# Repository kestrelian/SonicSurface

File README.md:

# SonicSurface
An Open ultrasonic phased-array for applications in acoustic levitation, haptic feedback, directive audio and many more.

## What's new here?
For our Capstone project, we designed a downsized array PCB for an 8 x 8 system. One FGPA (Waveshare/Altera) is responsible for 2 PCBs in contrast to the original SonicSurface implementation of 1 FGPA/baord.

# Contents of this Repository
Algorithms - Algorithms to generate different patterns (unchanged)
Electronics - PCB gerber files and bill of materials (PCB changed)
Firmware - Code to be upload in the FPGA boards that control the arrays (unchanged)
Mech - Mechanical parts for 3d printing or lasercutting (unchanged)

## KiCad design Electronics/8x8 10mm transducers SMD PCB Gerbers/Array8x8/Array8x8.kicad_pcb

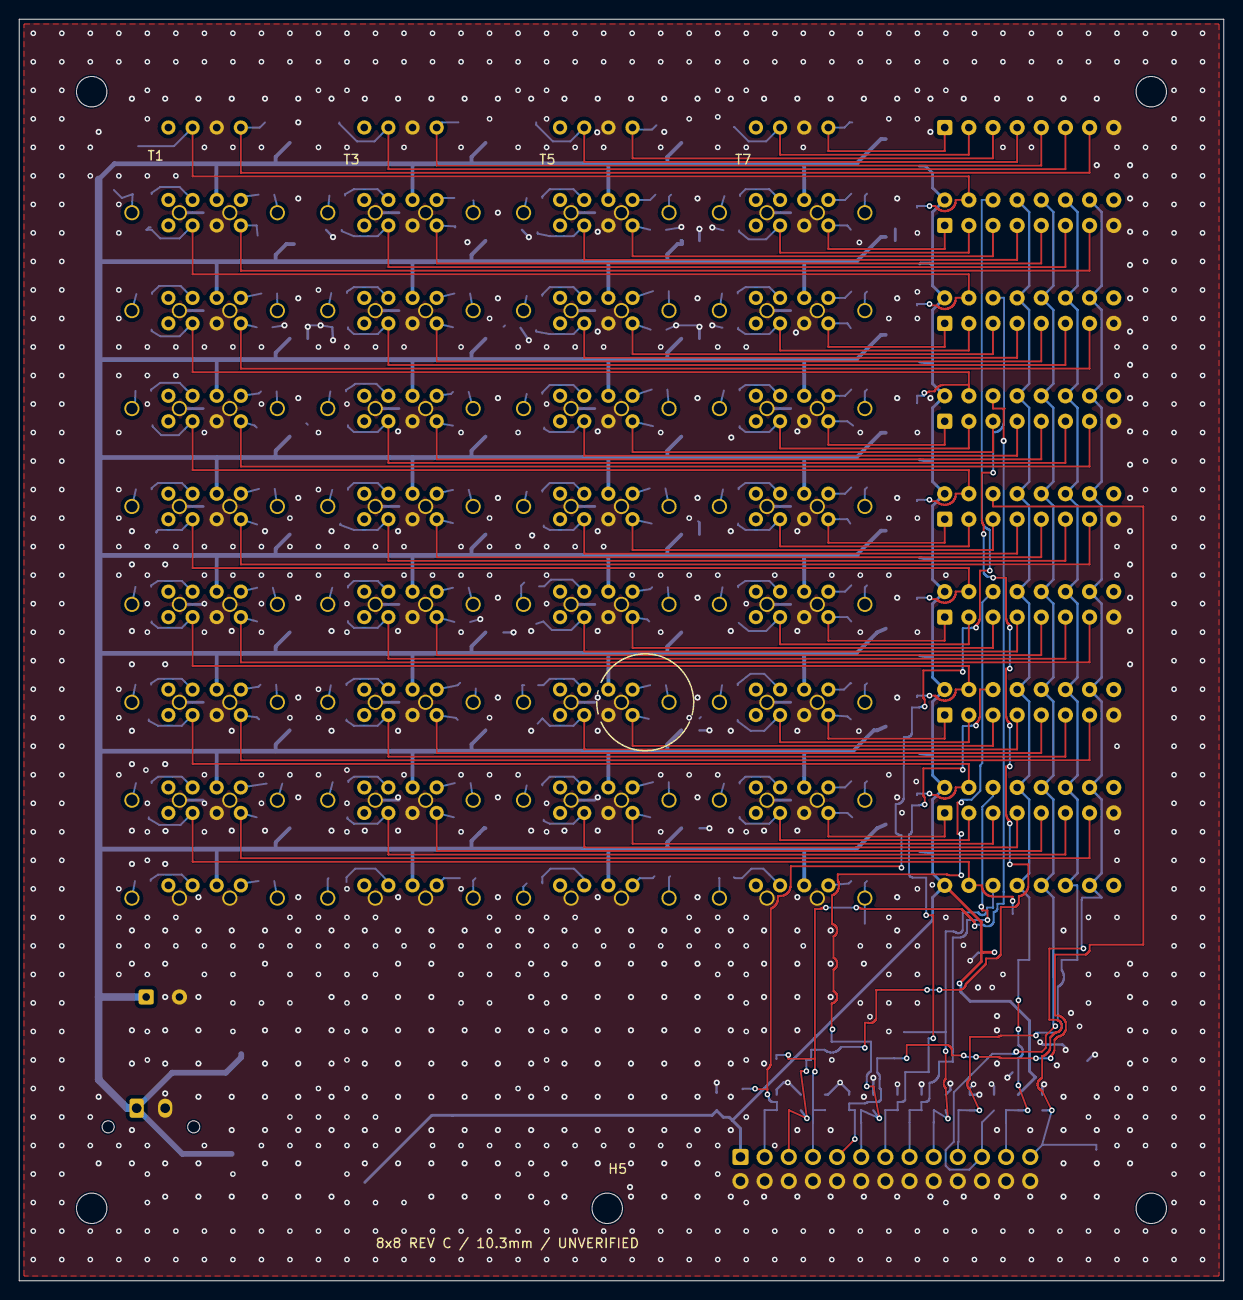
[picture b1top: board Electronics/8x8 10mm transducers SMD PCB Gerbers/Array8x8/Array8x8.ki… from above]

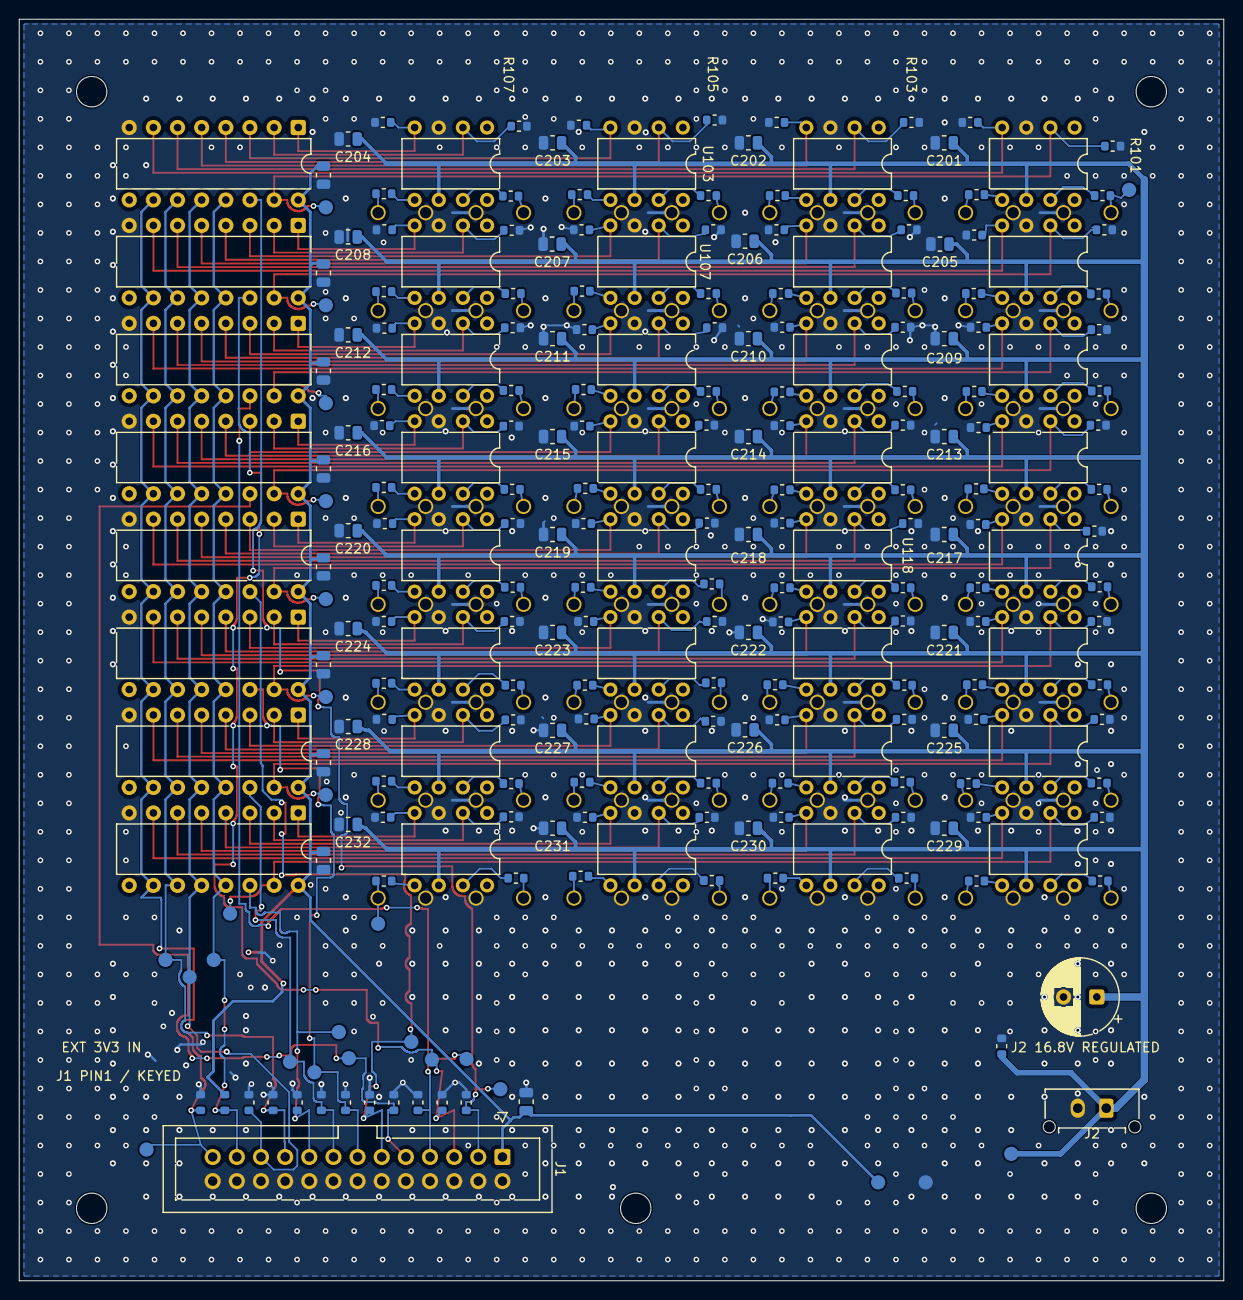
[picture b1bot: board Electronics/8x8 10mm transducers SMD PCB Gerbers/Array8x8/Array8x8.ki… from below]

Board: 2 copper layers, 126.7 x 132.7 mm, 319 parts (250 on the bottom side), 207 nets.

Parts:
C1: 220uF 35V low ESR; CP_Radial_D8.0mm_P3.50mm
C2, C10, C11, C12, C13, C14, C15, C16, C17, C201, C202, C203, C204, C205, C206, C207, C208, C209, C210, C211, C212, C213, C214, C215, C216, C217, C218, C219, C220, C221, C222, C223, C224, C225, C226, C227, C228, C229, C230, C231, C232: 1uF 50V X7R; C_0805_2012Metric
H1, H2, H3, H4, H5: MountingHole_3.2mm_M3
J1: KEYED IDC26 / 100mm MAX; IDC-Header_2x13_P2.54mm_Vertical
J2: REGULATED DRIVER POWER ONLY; FP_910b6471cdf1
R1, R20, R21, R22, R23, R24, R25, R26, R27, R28, R29, R30, R31, R101, R102, R103, R104, R105, R106, R107, R108, R109, R110, R111, R112, R113, R114, R115, R116, R117, R118, R119, R120, R121, R122, R123, R124, R125, R126, R127, R128, R129, R130, R131, R132, R133, R134, R135, R136, R137, R138, R139, R140, R141, R142, R143, R144, R145, R146, R147, R148, R149, R150, R151, R152, R153, R154, R155, R156, R157, R158, R159, R160, R161, R162, R163, R164: 10k; R_0603_1608Metric
R201, R202, R203, R204, R205, R206, R207, R208, R209, R210, R211, R212, R213, R214, R215, R216, R217, R218, R219, R220, R221, R222, R223, R224, R225, R226, R227, R228, R229, R230, R231, R232, R233, R234, R235, R236, R237, R238, R239, R240, R241, R242, R243, R244, R245, R246, R247, R248, R249, R250, R251, R252, R253, R254, R255, R256, R257, R258, R259, R260, R261, R262, R263, R264: 22R; R_0603_1608Metric
T1, T2, T3, T4, T5, T6, T7, T8, T9, T10, T11, T12, T13, T14, T15, T16, T17, T18, T19, T20, T21, T22, T23, T24, T25, T26, T27, T28, T29, T30, T31, T32, T33, T34, T35, T36, T37, T38, T39, T40, T41, T42, T43, T44, T45, T46, T47, T48, T49, T50, T51, T52, T53, T54, T55, T56, T57, T58, T59, T60, T61, T62, T63, T64: MA40S4S; MA40S4S_P5mm
TP1: GND; TestPoint_Pad_D1.5mm
TP2: +3V3; TestPoint_Pad_D1.5mm
TP3: VDRV; TestPoint_Pad_D1.5mm
TP4: SCLK; TestPoint_Pad_D1.5mm
TP5: LATCH; TestPoint_Pad_D1.5mm
TP6: OE_LOCAL_N; TestPoint_Pad_D1.5mm
TP8: DRV00; TestPoint_Pad_D1.5mm
TP9: DRV63; TestPoint_Pad_D1.5mm
TP10: Q00; TestPoint_Pad_D1.5mm
TP11: Q08; TestPoint_Pad_D1.5mm
TP12: Q16; TestPoint_Pad_D1.5mm
TP13: Q24; TestPoint_Pad_D1.5mm
TP14: Q32; TestPoint_Pad_D1.5mm
TP15: Q40; TestPoint_Pad_D1.5mm
TP16: Q48; TestPoint_Pad_D1.5mm
TP17: Q56; TestPoint_Pad_D1.5mm
TP18: DATA0_RX; TestPoint_Pad_D1.5mm
TP19: DATA1_RX; TestPoint_Pad_D1.5mm
TP20: DATA2_RX; TestPoint_Pad_D1.5mm
TP21: DATA3_RX; TestPoint_Pad_D1.5mm
TP22: DATA4_RX; TestPoint_Pad_D1.5mm
TP23: DATA5_RX; TestPoint_Pad_D1.5mm
TP24: DATA6_RX; TestPoint_Pad_D1.5mm
TP25: DATA7_RX; TestPoint_Pad_D1.5mm
TP26: CLR_N_RX; TestPoint_Pad_D1.5mm
U1, U2, U3, U4, U5, U6, U7, U8: SN74HC595N DIP-16; DIP-16_W7.62mm
U101, U102, U103, U104, U105, U106, U107, U108, U109, U110, U111, U112, U113, U114, U115, U116, U117, U118, U119, U120, U121, U122, U123, U124, U125, U126, U127, U128, U129, U130, U131, U132: TC4427EPA DIP-8; DIP-8_W7.62mm

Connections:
+3V3: C2.1, C10.1, C11.1, C12.1, C13.1, C14.1, C15.1, C16.1, C17.1, J1.1, R31.2, TP2.1, U1.16, U2.16, U3.16, U4.16, U5.16, U6.16, U7.16, U8.16
CLR_N_RX: J1.25, R30.1, TP26.1, U1.10, U2.10, U3.10, U4.10, U5.10, U6.10, U7.10, U8.10
DATA0_RX: J1.3, R20.1, TP18.1, U1.14
DATA1_RX: J1.5, R21.1, TP19.1, U2.14
DATA2_RX: J1.7, R22.1, TP20.1, U3.14
DATA3_RX: J1.9, R23.1, TP21.1, U4.14
DATA4_RX: J1.11, R24.1, TP22.1, U5.14
DATA5_RX: J1.13, R25.1, TP23.1, U6.14
DATA6_RX: J1.15, R26.1, TP24.1, U7.14
DATA7_RX: J1.17, R27.1, TP25.1, U8.14
DRV00: R201.2, T1.1, TP8.1
DRV01: R202.2, T2.1
DRV02: R203.2, T3.1
DRV03: R204.2, T4.1
DRV04: R205.2, T5.1
DRV05: R206.2, T6.1
DRV06: R207.2, T7.1
DRV07: R208.2, T8.1
DRV08: R209.2, T9.1
DRV09: R210.2, T10.1
DRV10: R211.2, T11.1
DRV11: R212.2, T12.1
DRV12: R213.2, T13.1
DRV13: R214.2, T14.1
DRV14: R215.2, T15.1
DRV15: R216.2, T16.1
DRV16: R217.2, T17.1
DRV17: R218.2, T18.1
DRV18: R219.2, T19.1
DRV19: R220.2, T20.1
DRV20: R221.2, T21.1
DRV21: R222.2, T22.1
DRV22: R223.2, T23.1
DRV23: R224.2, T24.1
DRV24: R225.2, T25.1
DRV25: R226.2, T26.1
DRV26: R227.2, T27.1
DRV27: R228.2, T28.1
DRV28: R229.2, T29.1
DRV29: R230.2, T30.1
DRV30: R231.2, T31.1
DRV31: R232.2, T32.1
DRV32: R233.2, T33.1
DRV33: R234.2, T34.1
DRV34: R235.2, T35.1
DRV35: R236.2, T36.1
DRV36: R237.2, T37.1
DRV37: R238.2, T38.1
DRV38: R239.2, T39.1
DRV39: R240.2, T40.1
DRV40: R241.2, T41.1
DRV41: R242.2, T42.1
DRV42: R243.2, T43.1
DRV43: R244.2, T44.1
DRV44: R245.2, T45.1
DRV45: R246.2, T46.1
DRV46: R247.2, T47.1
DRV47: R248.2, T48.1
DRV48: R249.2, T49.1
DRV49: R250.2, T50.1
DRV50: R251.2, T51.1
DRV51: R252.2, T52.1
DRV52: R253.2, T53.1
DRV53: R254.2, T54.1
DRV54: R255.2, T55.1
DRV55: R256.2, T56.1
DRV56: R257.2, T57.1
DRV57: R258.2, T58.1
DRV58: R259.2, T59.1
DRV59: R260.2, T60.1
DRV60: R261.2, T61.1
DRV61: R262.2, T62.1
DRV62: R263.2, T63.1
DRV63: R264.2, T64.1, TP9.1
GND: C1.2, C2.2, C10.2, C11.2, C12.2, C13.2, C14.2, C15.2, C16.2, C17.2, C201.2, C202.2, C203.2, C204.2, C205.2, C206.2, C207.2, C208.2, C209.2, C210.2, C211.2, C212.2, C213.2, C214.2, C215.2, C216.2, C217.2, C218.2, C219.2, C220.2, C221.2, C222.2, C223.2, C224.2, C225.2, C226.2, C227.2, C228.2, C229.2, C230.2, C231.2, C232.2, J1.2, J1.4, J1.6, J1.8, J1.10, J1.12, J1.14, J1.16, J1.18, J1.20, J1.22, J1.24, J1.26, J2.2, R1.2, R20.2, R21.2, R22.2, R23.2, R24.2, R25.2, R26.2, R27.2, R28.2, R29.2, R30.2, R101.2, R102.2, R103.2, R104.2, R105.2, R106.2, R107.2, R108.2, R109.2, R110.2, R111.2, R112.2, R113.2, R114.2, R115.2, R116.2, R117.2, R118.2, R119.2, R120.2, R121.2, R122.2, R123.2, R124.2, R125.2, R126.2, R127.2, R128.2, R129.2, R130.2, R131.2, R132.2, R133.2, R134.2, R135.2, R136.2, R137.2, R138.2, R139.2, R140.2, R141.2, R142.2, R143.2, R144.2, R145.2, R146.2, R147.2, R148.2, R149.2, R150.2, R151.2, R152.2, R153.2, R154.2, R155.2, R156.2, R157.2, R158.2, R159.2, R160.2, R161.2, R162.2, R163.2, R164.2, T1.2, T2.2, T3.2, T4.2, T5.2, T6.2, T7.2, T8.2, T9.2, T10.2, T11.2, T12.2, T13.2, T14.2, T15.2, T16.2, T17.2, T18.2, T19.2, T20.2, T21.2, T22.2, T23.2, T24.2, T25.2, T26.2, T27.2, T28.2, T29.2, T30.2, T31.2, T32.2, T33.2, T34.2, T35.2, T36.2, T37.2, T38.2, T39.2, T40.2, T41.2, T42.2, T43.2, T44.2, T45.2, T46.2, T47.2, T48.2, T49.2, T50.2, T51.2, T52.2, T53.2, T54.2, T55.2, T56.2, T57.2, T58.2, T59.2, T60.2, T61.2, T62.2, T63.2, T64.2, TP1.1, U1.8, U2.8, U3.8, U4.8, U5.8, U6.8, U7.8, U8.8, U101.3, U102.3, U103.3, U104.3, U105.3, U106.3, U107.3, U108.3, U109.3, U110.3, U111.3, U112.3, U113.3, U114.3, U115.3, U116.3, U117.3, U118.3, U119.3, U120.3, U121.3, U122.3, U123.3, U124.3, U125.3, U126.3, U127.3, U128.3, U129.3, U130.3, U131.3, U132.3
LATCH_RX: J1.21, R29.1, TP5.1, U1.12, U2.12, U3.12, U4.12, U5.12, U6.12, U7.12, U8.12
OE_N_RX: J1.23, R31.1, TP6.1, U1.13, U2.13, U3.13, U4.13, U5.13, U6.13, U7.13, U8.13
OUT00: R201.1, U101.7
OUT01: R202.1, U101.5
OUT02: R203.1, U102.7
OUT03: R204.1, U102.5
OUT04: R205.1, U103.7
OUT05: R206.1, U103.5
OUT06: R207.1, U104.7
OUT07: R208.1, U104.5
OUT08: R209.1, U105.7
OUT09: R210.1, U105.5
OUT10: R211.1, U106.7
OUT11: R212.1, U106.5
OUT12: R213.1, U107.7
OUT13: R214.1, U107.5
OUT14: R215.1, U108.7
OUT15: R216.1, U108.5
OUT16: R217.1, U109.7
OUT17: R218.1, U109.5
OUT18: R219.1, U110.7
OUT19: R220.1, U110.5
OUT20: R221.1, U111.7
OUT21: R222.1, U111.5
OUT22: R223.1, U112.7
OUT23: R224.1, U112.5
OUT24: R225.1, U113.7
OUT25: R226.1, U113.5
OUT26: R227.1, U114.7
OUT27: R228.1, U114.5
OUT28: R229.1, U115.7
OUT29: R230.1, U115.5
OUT30: R231.1, U116.7
OUT31: R232.1, U116.5
OUT32: R233.1, U117.7
OUT33: R234.1, U117.5
OUT34: R235.1, U118.7
OUT35: R236.1, U118.5
OUT36: R237.1, U119.7
OUT37: R238.1, U119.5
OUT38: R239.1, U120.7
OUT39: R240.1, U120.5
OUT40: R241.1, U121.7
OUT41: R242.1, U121.5
OUT42: R243.1, U122.7
OUT43: R244.1, U122.5
OUT44: R245.1, U123.7
OUT45: R246.1, U123.5
OUT46: R247.1, U124.7
OUT47: R248.1, U124.5
OUT48: R249.1, U125.7
OUT49: R250.1, U125.5
OUT50: R251.1, U126.7
OUT51: R252.1, U126.5
OUT52: R253.1, U127.7
OUT53: R254.1, U127.5
OUT54: R255.1, U128.7
OUT55: R256.1, U128.5
OUT56: R257.1, U129.7
OUT57: R258.1, U129.5
OUT58: R259.1, U130.7
OUT59: R260.1, U130.5
OUT60: R261.1, U131.7
OUT61: R262.1, U131.5
OUT62: R263.1, U132.7
OUT63: R264.1, U132.5
Q00: R101.1, TP10.1, U1.15, U101.2
Q01: R102.1, U1.7, U101.4
Q02: R103.1, U1.6, U102.2
Q03: R104.1, U1.5, U102.4
Q04: R105.1, U1.4, U103.2
Q05: R106.1, U1.3, U103.4
Q06: R107.1, U1.2, U104.2
Q07: R108.1, U1.1, U104.4
Q08: R109.1, TP11.1, U2.15, U105.2
Q09: R110.1, U2.7, U105.4
Q10: R111.1, U2.6, U106.2
Q11: R112.1, U2.5, U106.4
Q12: R113.1, U2.4, U107.2
Q13: R114.1, U2.3, U107.4
Q14: R115.1, U2.2, U108.2
Q15: R116.1, U2.1, U108.4
Q16: R117.1, TP12.1, U3.15, U109.2
Q17: R118.1, U3.7, U109.4
Q18: R119.1, U3.6, U110.2
Q19: R120.1, U3.5, U110.4
Q20: R121.1, U3.4, U111.2
Q21: R122.1, U3.3, U111.4
Q22: R123.1, U3.2, U112.2
Q23: R124.1, U3.1, U112.4
Q24: R125.1, TP13.1, U4.15, U113.2
Q25: R126.1, U4.7, U113.4
Q26: R127.1, U4.6, U114.2
Q27: R128.1, U4.5, U114.4
Q28: R129.1, U4.4, U115.2
Q29: R130.1, U4.3, U115.4
Q30: R131.1, U4.2, U116.2
Q31: R132.1, U4.1, U116.4
Q32: R133.1, TP14.1, U5.15, U117.2
Q33: R134.1, U5.7, U117.4
Q34: R135.1, U5.6, U118.2
Q35: R136.1, U5.5, U118.4
Q36: R137.1, U5.4, U119.2
Q37: R138.1, U5.3, U119.4
Q38: R139.1, U5.2, U120.2
Q39: R140.1, U5.1, U120.4
Q40: R141.1, TP15.1, U6.15, U121.2
Q41: R142.1, U6.7, U121.4
Q42: R143.1, U6.6, U122.2
Q43: R144.1, U6.5, U122.4
Q44: R145.1, U6.4, U123.2
Q45: R146.1, U6.3, U123.4
Q46: R147.1, U6.2, U124.2
Q47: R148.1, U6.1, U124.4
Q48: R149.1, TP16.1, U7.15, U125.2
Q49: R150.1, U7.7, U125.4
Q50: R151.1, U7.6, U126.2
Q51: R152.1, U7.5, U126.4
Q52: R153.1, U7.4, U127.2
Q53: R154.1, U7.3, U127.4
Q54: R155.1, U7.2, U128.2
Q55: R156.1, U7.1, U128.4
Q56: R157.1, TP17.1, U8.15, U129.2
Q57: R158.1, U8.7, U129.4
Q58: R159.1, U8.6, U130.2
Q59: R160.1, U8.5, U130.4
Q60: R161.1, U8.4, U131.2
Q61: R162.1, U8.3, U131.4
Q62: R163.1, U8.2, U132.2
Q63: R164.1, U8.1, U132.4
SCLK_RX: J1.19, R28.1, TP4.1, U1.11, U2.11, U3.11, U4.11, U5.11, U6.11, U7.11, U8.11
VDRV: C1.1, C201.1, C202.1, C203.1, C204.1, C205.1, C206.1, C207.1, C208.1, C209.1, C210.1, C211.1, C212.1, C213.1, C214.1, C215.1, C216.1, C217.1, C218.1, C219.1, C220.1, C221.1, C222.1, C223.1, C224.1, C225.1, C226.1, C227.1, C228.1, C229.1, C230.1, C231.1, C232.1, J2.1, R1.1, TP3.1, U101.6, U102.6, U103.6, U104.6, U105.6, U106.6, U107.6, U108.6, U109.6, U110.6, U111.6, U112.6, U113.6, U114.6, U115.6, U116.6, U117.6, U118.6, U119.6, U120.6, U121.6, U122.6, U123.6, U124.6, U125.6, U126.6, U127.6, U128.6, U129.6, U130.6, U131.6, U132.6

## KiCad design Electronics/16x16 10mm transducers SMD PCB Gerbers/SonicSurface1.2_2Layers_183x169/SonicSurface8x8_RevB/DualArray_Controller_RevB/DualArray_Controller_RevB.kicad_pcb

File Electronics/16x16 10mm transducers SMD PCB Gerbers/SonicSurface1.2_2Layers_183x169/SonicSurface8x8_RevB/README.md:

# SonicSurface dual 8x8 hardware — Revision B

26 October 2026. **Engineering draft. Final verification NOT EXECUTED. Not a fabrication release.**

This revision supersedes Rev A for the requested new hardware. Rev A files are preserved separately. Build two identical array PCBs and one controller/power adapter.

## Native KiCad projects

- `Array8x8_RevB/Array8x8_RevB.kicad_pro`: two-layer 114 × 120 mm array, 64 MA40S4S at 10.3 mm pitch, 32 TC4427EPA DIP-8 and eight SN74HC595N DIP-16. The front is acoustic; drivers and interface components are on the back.
- `DualArray_Controller_RevB/DualArray_Controller_RevB.kicad_pro`: two-layer 120 × 140 mm controller/power adapter. It mates with CoreEP4CE6 P1, has two separately buffered IDC26 signal outputs, a 17–20 V input and two protected driver-power outputs.
- Each project includes local symbols/footprints, schematic SVGs, BOMs, intended connectivity, placement exports and an `authoring` directory.
- `fabrication_UNVERIFIED` contains generated manufacturing files after routing import. These are not approved manufacturing releases.

## Electrical arrangement

External 17–20 V input → 2 A fuse → TPS26600 input protection → LTC3115-1 buck-boost set to 16.8 V → LTC4365 precision window cutoff and back-to-back MOSFETs → separate 750 mA fuses and power cables to the arrays.

The adapter's separate R-78E3.3-0.5 regulator supplies both arrays' logic. Core P1 pin 2 is used only for voltage sensing and source-side bias, not as a logic-power source. Core P1 pin 24 remains unconnected. Power the Core module through its own approved input.

Each array has input buffers with partial-power-down protection, logic and driver-rail supervisors, hardware gating of the HC595 output enable, input pulldowns, 22 Ω output damping resistors, a discharge resistor and test points. Two copies use identical connectors and circuitry; adapter port A/B selects the channel bank.

The actual driver rail is slightly below the 16.8 V regulator setpoint because of MOSFET, fuse, connector and cable losses. Neither connector is a raw 20 V driver input. See `POWER_DESIGN.md` for voltage margins and remaining transient evidence requirements.

## Files for external firmware/software projects

`HARDWARE_INTERFACE.md`, `FPGA_INTERFACE.csv`, `CABLE_PIN_MAP.csv`, `CHANNEL_MAP.csv` and `CoreEP4CE6_DualArray_pins.qsf` define the hardware contract. The QSF is a pin fragment only. No firmware, host software, Quartus build, timing simulation or bitstream is included.

Use two straight keyed IDC26 cables with integral strain-relief covers, each no longer than 100 mm. The provisional hardware interface ceiling is 4 MHz shift clock; it is a design requirement pending signal-integrity validation, not a measured capability. Driver power uses separate keyed Micro-Fit cables. No hot-plug qualification is claimed.

## Mechanical changes

Array area decreases from 19,840 mm² (160 × 124 mm) to 13,680 mm² (114 × 120 mm), about 31.0%. The transducer body envelope is 82.3 × 82.3 mm using maximum 10.2 mm diameter. A 10.3 mm pitch gives only 0.1 mm nominal gap at maximum body diameter. Positional tolerance and assembly fit are release gates.

Each TC4427 sits on the back between two transducer rows, rotated so its inputs face the row above and its outputs face its own row. This keeps even a maximum-length 10.16 mm PDIP body clear of the transducer leads and leaves an eight-track front-copper channel through every driver row. The HC595 outputs run left in that channel straight into the driver inputs. As a result, the shift-register output order is QA→column 0 and QB..QH→columns 7..1 (see `HARDWARE_INTERFACE.md`). Transducers alternate 180° in each driver pair so pin 1 (drive) is always the outer pin.

The 1.2 mm transducer holes use 1.6 mm round copper pads (0.20 mm nominal annular ring); TC4427 DIP pads are round 1.5 mm on 0.8 mm holes. Pin 1 is identified by graphics/reference documentation, not a square pad. The layout uses 0.15 mm minimum clearance, 0.2 mm signal tracks and 0.6/0.3 mm vias; it needs fabricator and physical-fit review. Do not substitute generic footprints without re-layout.

## Status and reproduction

Final ERC, DRC, independent CAM review, electrical tests and acoustic measurements remain deliberately unexecuted. See `QA_CHECKLIST.md`. Router counts and file-export success are authoring information only.

`build_revb.py` regenerates placed boards and schematics and overwrites generated edits. For the array, `relayout_array.py` then applies the row-channel placement and writes the structured array copper as locked tracks; `relayout_array.py --schematic` applies the matching HC595 output labels to the row sheets (run it once per rebuild). `route_array.py prepare` adds ground escapes and writes `authoring/interface.dsn`; route it with Freerouting 2.5.0 (fan-out and optimizer disabled) to `authoring/interface.ses`; `route_array.py import` imports the session and pours ground. The controller still uses `prepare_routing.py` / `import_routing.py`. `export_fabrication.py` creates fabrication exports. Copy the project before rebuilding.

Everything stays local. No push, order or upload is part of this work.

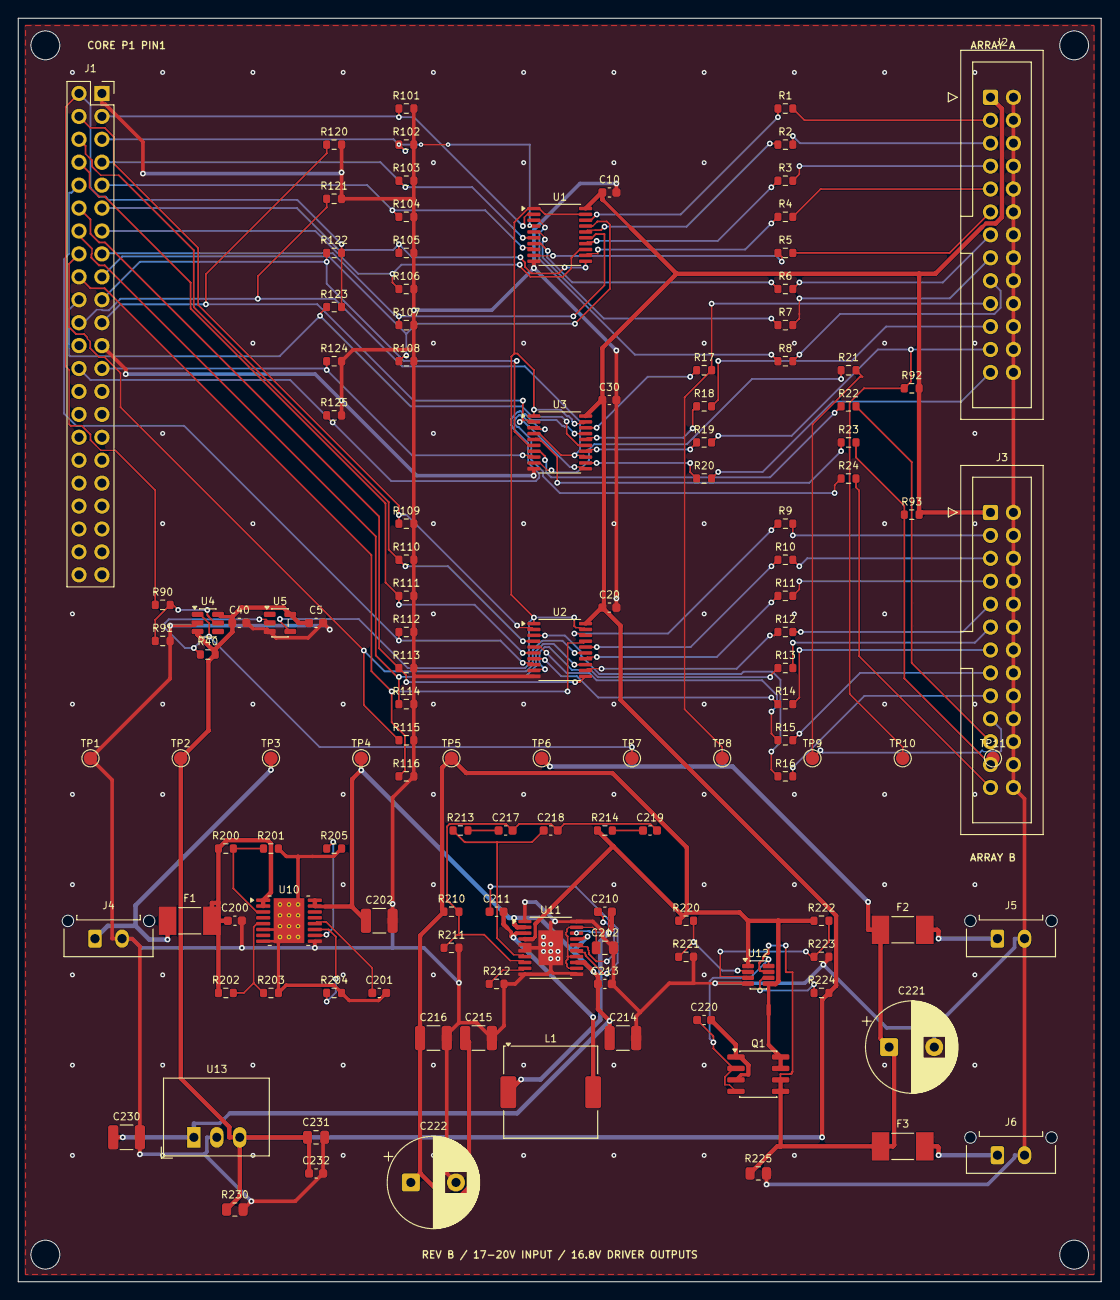
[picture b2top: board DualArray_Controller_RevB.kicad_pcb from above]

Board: 2 copper layers, 120.0 x 140.0 mm, 128 parts (0 on the bottom side), 104 nets.

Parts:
C5, C10, C20, C30, C40, C200, C201, C210, C211, C213, C232: 100nF 50V X7R; C_0603_1608Metric
C202, C214, C230: 10uF 50V X7R; C_1210_3225Metric
C212: 4.7uF 10V X7R; C_0805_2012Metric
C215, C216: 22uF 50V X7R; C_1210_3225Metric
C217: 8.2nF C0G; C_0603_1608Metric
C218: 150pF C0G; C_0603_1608Metric
C219: 1nF C0G; C_0603_1608Metric
C220: 47nF 50V X7R; C_0603_1608Metric
C221, C222: 470uF 35V low ESR; CP_Radial_D10.0mm_P5.00mm
C231: 10uF 10V X7R; C_0805_2012Metric
F1: 0451002.MRL / 2A 125V; Fuse_Littelfuse-NANO2-451_453
F2, F3: 0451.750MRL / 750mA 125V; Fuse_Littelfuse-NANO2-451_453
H1, H2, H3, H4: MountingHole_3.2mm_M3
J1: CoreEP4CE6 P1 / POWER PINS ISOLATED; PinSocket_2x22_P2.54mm_Vertical
J2: KEYED IDC26 / ARRAY A; IDC-Header_2x13_P2.54mm_Vertical
J3: KEYED IDC26 / ARRAY B; IDC-Header_2x13_P2.54mm_Vertical
J4: 17-20V DC INPUT; FP_910b6471cdf1
J5: 16.8V POWER ARRAY A; FP_910b6471cdf1
J6: 16.8V POWER ARRAY B; FP_910b6471cdf1
L1: 15uH MSS1048-153MLB; L_Coilcraft_MSS1048-XXX
Q1: Si9945CDY-T1-GE3; SOIC-8_3.9x4.9mm_P1.27mm
R1, R2, R3, R4, R5, R6, R7, R8, R9, R10, R11, R12, R13, R14, R15, R16, R17, R18, R19, R20, R21, R22, R23, R24: 33R source; R_0603_1608Metric
R40, R92, R93, R205, R224: 10k; R_0603_1608Metric
R90: 64.9k 0.1%; R_0603_1608Metric
R91, R201, R203, R211, R221: 10k 0.1%; R_0603_1608Metric
R101, R102, R103, R104, R105, R106, R107, R108, R109, R110, R111, R112, R113, R114, R115, R116, R120, R121, R122, R123, R124, R125: 100k; R_0603_1608Metric
R200: 121k 0.1%; R_0603_1608Metric
R202: 178k 0.1%; R_0603_1608Metric
R204: 8.06k 1%; R_0603_1608Metric
R210: 158k 0.1%; R_0603_1608Metric
R212: 47.5k 1%; R_0603_1608Metric
R213: 18k 1%; R_0603_1608Metric
R214: 2.67k 1%; R_0603_1608Metric
R220: 290k 0.1%; R_0603_1608Metric
R222: 340k 0.01%; R_0603_1608Metric
R223: 10k 0.01%; R_0603_1608Metric
R225: 10k 0.25W; R_0805_2012Metric
R230: 330R 0.125W minimum load; R_0805_2012Metric
TP1: GND; TestPoint_Pad_D1.5mm
TP2: +3V3; TestPoint_Pad_D1.5mm
TP3: VIN; TestPoint_Pad_D1.5mm
TP4: VPROT; TestPoint_Pad_D1.5mm
TP5: VREG_16V8; TestPoint_Pad_D1.5mm
TP6: VDRV_SAFE; TestPoint_Pad_D1.5mm
TP7: CORE_OK; TestPoint_Pad_D1.5mm
TP8: A_SCLK; TestPoint_Pad_D1.5mm
TP9: B_SCLK; TestPoint_Pad_D1.5mm
TP10: A_OE_N; TestPoint_Pad_D1.5mm
TP11: B_OE_N; TestPoint_Pad_D1.5mm
U1, U2, U3: SN74LVC244APW / Ioff; TSSOP-20_4.4x6.5mm_P0.65mm
U4: TPS3808G01DBVR; SOT-23-6
U5: SN74LVC1G04DBVR; SOT-23-5
U10: TPS26600PWPR; FP_eae3e738c928
U11: LTC3115IFE-1#PBF; FP_e5b083f4a3ae
U12: LTC4365ITS8#PBF; TSOT-23-8
U13: R-78E3.3-0.5; Converter_DCDC_RECOM_R-78E-0.5_THT

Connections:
+3V3: C5.1, C10.1, C20.1, C30.1, C40.1, C231.1, C232.1, J2.1, J3.1, R40.2, R92.2, R93.2, R224.2, R230.1, TP2.1, U1.20, U2.20, U3.20, U4.3, U4.6, U5.5, U13.3
A_CLR_N: J2.25, R20.2
A_CLR_N_BUF: R20.1, U3.12
A_CLR_N_SRC: J1.25, R124.1, U3.8
A_DATA0: J2.3, R1.2
A_DATA0_BUF: R1.1, U1.18
A_DATA0_SRC: J1.3, R101.1, U1.2
A_DATA1: J2.5, R2.2
A_DATA1_BUF: R2.1, U1.16
A_DATA1_SRC: J1.5, R102.1, U1.4
A_DATA2: J2.7, R3.2
A_DATA2_BUF: R3.1, U1.14
A_DATA2_SRC: J1.7, R103.1, U1.6
A_DATA3: J2.9, R4.2
A_DATA3_BUF: R4.1, U1.12
A_DATA3_SRC: J1.9, R104.1, U1.8
A_DATA4: J2.11, R5.2
A_DATA4_BUF: R5.1, U1.9
A_DATA4_SRC: J1.11, R105.1, U1.11
A_DATA5: J2.13, R6.2
A_DATA5_BUF: R6.1, U1.7
A_DATA5_SRC: J1.13, R106.1, U1.13
A_DATA6: J2.15, R7.2
A_DATA6_BUF: R7.1, U1.5
A_DATA6_SRC: J1.15, R107.1, U1.15
A_DATA7: J2.17, R8.2
A_DATA7_BUF: R8.1, U1.3
A_DATA7_SRC: J1.17, R108.1, U1.17
A_LATCH: J2.21, R18.2
A_LATCH_BUF: R18.1, U3.16
A_OE_N: J2.23, R19.2, R92.1, TP10.1
A_OE_N_BUF: R19.1, U3.14
A_OE_N_SRC: J1.19, R122.1, U3.6
A_SCLK: J2.19, R17.2, TP8.1
A_SCLK_BUF: R17.1, U3.18
BST1: C210.1, U11.16
BST2: C211.1, U11.15
B_CLR_N: J3.25, R24.2
B_CLR_N_BUF: R24.1, U3.3
B_CLR_N_SRC: J1.26, R125.1, U3.17
B_DATA0: J3.3, R9.2
B_DATA0_BUF: R9.1, U2.18
B_DATA0_SRC: J1.4, R109.1, U2.2
B_DATA1: J3.5, R10.2
B_DATA1_BUF: R10.1, U2.16
B_DATA1_SRC: J1.6, R110.1, U2.4
B_DATA2: J3.7, R11.2
B_DATA2_BUF: R11.1, U2.14
B_DATA2_SRC: J1.8, R111.1, U2.6
B_DATA3: J3.9, R12.2
B_DATA3_BUF: R12.1, U2.12
B_DATA3_SRC: J1.10, R112.1, U2.8
B_DATA4: J3.11, R13.2
B_DATA4_BUF: R13.1, U2.9
B_DATA4_SRC: J1.12, R113.1, U2.11
B_DATA5: J3.13, R14.2
B_DATA5_BUF: R14.1, U2.7
B_DATA5_SRC: J1.14, R114.1, U2.13
B_DATA6: J3.15, R15.2
B_DATA6_BUF: R15.1, U2.5
B_DATA6_SRC: J1.16, R115.1, U2.15
B_DATA7: J3.17, R16.2
B_DATA7_BUF: R16.1, U2.3
B_DATA7_SRC: J1.18, R116.1, U2.17
B_LATCH: J3.21, R22.2
B_LATCH_BUF: R22.1, U3.7
B_OE_N: J3.23, R23.2, R93.1, TP11.1
B_OE_N_BUF: R23.1, U3.5
B_OE_N_SRC: J1.20, R123.1, U3.15
B_SCLK: J3.19, R21.2, TP9.1
B_SCLK_BUF: R21.1, U3.9
COMP: C217.1, R213.2
CORE_3V3_SENSE: J1.2, R90.1, R122.2, R123.2
CORE_BAD: U1.1, U1.19, U2.1, U2.19, U3.1, U3.19, U5.4
CORE_OK: R40.1, TP7.1, U4.1, U5.2
CORE_SENSE_DIV: R90.2, R91.1, U4.5
FB: C217.2, C218.2, C219.2, R210.2, R211.1, U11.8
FET_COMMON: C220.2, Q1.1, Q1.3
FF: C219.1, R214.2
GND: C5.2, C10.2, C20.2, C30.2, C40.2, C200.2, C202.2, C212.2, C213.2, C214.2, C215.2, C216.2, C221.2, C222.2, C230.2, C231.2, C232.2, J1.1, J1.23, J2.2, J2.4, J2.6, J2.8, J2.10, J2.12, J2.14, J2.16, J2.18, J2.20, J2.22, J2.24, J2.26, J3.2, J3.4, J3.6, J3.8, J3.10, J3.12, J3.14, J3.16, J3.18, J3.20, J3.22, J3.24, J3.26, J4.2, J5.2, J6.2, R91.2, R101.2, R102.2, R103.2, R104.2, R105.2, R106.2, R107.2, R108.2, R109.2, R110.2, R111.2, R112.2, R113.2, R114.2, R115.2, R116.2, R120.2, R121.2, R124.2, R125.2, R211.2, R212.2, R221.2, R223.2, R225.2, R230.2, TP1.1, U1.10, U2.10, U3.10, U4.2, U5.3, U10.9, U11.1, U11.5, U11.6, U11.10, U11.11, U11.20, U11.21, U12.4, U13.2
IN_DVDT: C201.1, U10.12
IN_ILIM: R204.1, U10.11
IN_IMON: R205.1, U10.10
IN_OV: R202.2, R203.1, U10.5
IN_RTN: C201.2, R201.2, R203.2, R204.2, R205.2, U10.6, U10.8, U10.17
IN_UV: R200.2, R201.1, U10.3
LATCH_SRC: J1.22, R121.1, U3.4, U3.13
OUT_FAULT_N: R224.1, U12.6
OUT_OV: R222.2, R223.1, U12.3
OUT_UV: R220.2, R221.1, U12.2
PASS_GATE: C220.1, Q1.2, Q1.4, U12.8
RT: R212.1, U11.9
SCLK_SRC: J1.21, R120.1, U3.2, U3.11
SW1: C210.2, L1.1, U11.18
SW2: C211.2, L1.2, U11.3
VC: C218.1, R213.1, U11.7
VCC_BB: C212.1, U11.12, U11.14, U11.19
VDRV_A: F2.2, J5.1
VDRV_B: F3.2, J6.1
VDRV_SAFE: C221.1, F2.1, F3.1, Q1.5, Q1.6, R225.1, TP6.1, U12.7
VIN: F1.1, J4.1, TP3.1
VINPUT_FUSED: C200.1, F1.2, R200.1, R202.1, U10.1, U10.2
VPROT: C202.1, C213.1, C214.1, C230.1, TP4.1, U10.15, U10.16, U11.2, U11.13, U11.17, U13.1
VREG_16V8: C215.1, C216.1, C222.1, Q1.7, Q1.8, R210.1, R214.1, R220.1, R222.1, TP5.1, U11.4, U12.1, U12.5

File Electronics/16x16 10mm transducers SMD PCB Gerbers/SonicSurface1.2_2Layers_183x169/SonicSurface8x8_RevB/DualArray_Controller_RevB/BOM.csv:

Reference,Value / part,Footprint,Quantity,Notes
J1,CoreEP4CE6 P1 / POWER PINS ISOLATED,SS8:PinSocket_2x22_P2.54mm_Vertical,1,Unverified Rev B
U4,TPS3808G01DBVR,SS8:SOT-23-6,1,Unverified Rev B
C40,100nF 50V X7R,SS8:C_0603_1608Metric,1,Unverified Rev B
R40,10k,SS8:R_0603_1608Metric,1,Unverified Rev B
R90,64.9k 0.1%,SS8:R_0603_1608Metric,1,Unverified Rev B
R91,10k 0.1%,SS8:R_0603_1608Metric,1,Unverified Rev B
U5,SN74LVC1G04DBVR,SS8:SOT-23-5,1,Unverified Rev B
C5,100nF 50V X7R,SS8:C_0603_1608Metric,1,Unverified Rev B
J2,KEYED IDC26 / ARRAY A,SS8:IDC-Header_2x13_P2.54mm_Vertical,1,Unverified Rev B
U1,SN74LVC244APW / Ioff,SS8:TSSOP-20_4.4x6.5mm_P0.65mm,1,Unverified Rev B
C10,100nF 50V X7R,SS8:C_0603_1608Metric,1,Unverified Rev B
R1,33R source,SS8:R_0603_1608Metric,1,Unverified Rev B
R101,100k,SS8:R_0603_1608Metric,1,Unverified Rev B
R2,33R source,SS8:R_0603_1608Metric,1,Unverified Rev B
R102,100k,SS8:R_0603_1608Metric,1,Unverified Rev B
R3,33R source,SS8:R_0603_1608Metric,1,Unverified Rev B
R103,100k,SS8:R_0603_1608Metric,1,Unverified Rev B
R4,33R source,SS8:R_0603_1608Metric,1,Unverified Rev B
R104,100k,SS8:R_0603_1608Metric,1,Unverified Rev B
R5,33R source,SS8:R_0603_1608Metric,1,Unverified Rev B
R105,100k,SS8:R_0603_1608Metric,1,Unverified Rev B
R6,33R source,SS8:R_0603_1608Metric,1,Unverified Rev B
R106,100k,SS8:R_0603_1608Metric,1,Unverified Rev B
R7,33R source,SS8:R_0603_1608Metric,1,Unverified Rev B
R107,100k,SS8:R_0603_1608Metric,1,Unverified Rev B
R8,33R source,SS8:R_0603_1608Metric,1,Unverified Rev B
R108,100k,SS8:R_0603_1608Metric,1,Unverified Rev B
J3,KEYED IDC26 / ARRAY B,SS8:IDC-Header_2x13_P2.54mm_Vertical,1,Unverified Rev B
U2,SN74LVC244APW / Ioff,SS8:TSSOP-20_4.4x6.5mm_P0.65mm,1,Unverified Rev B
C20,100nF 50V X7R,SS8:C_0603_1608Metric,1,Unverified Rev B
R9,33R source,SS8:R_0603_1608Metric,1,Unverified Rev B
R109,100k,SS8:R_0603_1608Metric,1,Unverified Rev B
R10,33R source,SS8:R_0603_1608Metric,1,Unverified Rev B
R110,100k,SS8:R_0603_1608Metric,1,Unverified Rev B
R11,33R source,SS8:R_0603_1608Metric,1,Unverified Rev B
R111,100k,SS8:R_0603_1608Metric,1,Unverified Rev B
R12,33R source,SS8:R_0603_1608Metric,1,Unverified Rev B
R112,100k,SS8:R_0603_1608Metric,1,Unverified Rev B
R13,33R source,SS8:R_0603_1608Metric,1,Unverified Rev B
R113,100k,SS8:R_0603_1608Metric,1,Unverified Rev B
R14,33R source,SS8:R_0603_1608Metric,1,Unverified Rev B
R114,100k,SS8:R_0603_1608Metric,1,Unverified Rev B
R15,33R source,SS8:R_0603_1608Metric,1,Unverified Rev B
R115,100k,SS8:R_0603_1608Metric,1,Unverified Rev B
R16,33R source,SS8:R_0603_1608Metric,1,Unverified Rev B
R116,100k,SS8:R_0603_1608Metric,1,Unverified Rev B
U3,SN74LVC244APW / Ioff,SS8:TSSOP-20_4.4x6.5mm_P0.65mm,1,Unverified Rev B
C30,100nF 50V X7R,SS8:C_0603_1608Metric,1,Unverified Rev B
R17,33R source,SS8:R_0603_1608Metric,1,Unverified Rev B
R18,33R source,SS8:R_0603_1608Metric,1,Unverified Rev B
R19,33R source,SS8:R_0603_1608Metric,1,Unverified Rev B
R20,33R source,SS8:R_0603_1608Metric,1,Unverified Rev B
R21,33R source,SS8:R_0603_1608Metric,1,Unverified Rev B
R22,33R source,SS8:R_0603_1608Metric,1,Unverified Rev B
R23,33R source,SS8:R_0603_1608Metric,1,Unverified Rev B
R24,33R source,SS8:R_0603_1608Metric,1,Unverified Rev B
R120,100k,SS8:R_0603_1608Metric,1,Unverified Rev B
R121,100k,SS8:R_0603_1608Metric,1,Unverified Rev B
R122,100k,SS8:R_0603_1608Metric,1,Unverified Rev B
R123,100k,SS8:R_0603_1608Metric,1,Unverified Rev B
R124,100k,SS8:R_0603_1608Metric,1,Unverified Rev B
R125,100k,SS8:R_0603_1608Metric,1,Unverified Rev B
R92,10k,SS8:R_0603_1608Metric,1,Unverified Rev B
R93,10k,SS8:R_0603_1608Metric,1,Unverified Rev B
J4,17-20V DC INPUT,SS8:FP_910b6471cdf1,1,Unverified Rev B
F1,0451002.MRL / 2A 125V,SS8:Fuse_Littelfuse-NANO2-451_453,1,Unverified Rev B
U10,TPS26600PWPR,SS8:FP_eae3e738c928,1,Unverified Rev B
R200,121k 0.1%,SS8:R_0603_1608Metric,1,Unverified Rev B
R201,10k 0.1%,SS8:R_0603_1608Metric,1,Unverified Rev B
R202,178k 0.1%,SS8:R_0603_1608Metric,1,Unverified Rev B
R203,10k 0.1%,SS8:R_0603_1608Metric,1,Unverified Rev B
R204,8.06k 1%,SS8:R_0603_1608Metric,1,Unverified Rev B
R205,10k,SS8:R_0603_1608Metric,1,Unverified Rev B
C200,100nF 50V X7R,SS8:C_0603_1608Metric,1,Unverified Rev B
C201,100nF 50V X7R,SS8:C_0603_1608Metric,1,Unverified Rev B
C202,10uF 50V X7R,SS8:C_1210_3225Metric,1,Unverified Rev B
U11,LTC3115IFE-1#PBF,SS8:FP_e5b083f4a3ae,1,Unverified Rev B
L1,15uH MSS1048-153MLB,SS8:L_Coilcraft_MSS1048-XXX,1,Unverified Rev B
C210,100nF 50V X7R,SS8:C_0603_1608Metric,1,Unverified Rev B
C211,100nF 50V X7R,SS8:C_0603_1608Metric,1,Unverified Rev B
C212,4.7uF 10V X7R,SS8:C_0805_2012Metric,1,Unverified Rev B
C213,100nF 50V X7R,SS8:C_0603_1608Metric,1,Unverified Rev B
C214,10uF 50V X7R,SS8:C_1210_3225Metric,1,Unverified Rev B
C215,22uF 50V X7R,SS8:C_1210_3225Metric,1,Unverified Rev B
C216,22uF 50V X7R,SS8:C_1210_3225Metric,1,Unverified Rev B
C217,8.2nF C0G,SS8:C_0603_1608Metric,1,Unverified Rev B
C218,150pF C0G,SS8:C_0603_1608Metric,1,Unverified Rev B
R210,158k 0.1%,SS8:R_0603_1608Metric,1,Unverified Rev B
R211,10k 0.1%,SS8:R_0603_1608Metric,1,Unverified Rev B
R212,47.5k 1%,SS8:R_0603_1608Metric,1,Unverified Rev B
R213,18k 1%,SS8:R_0603_1608Metric,1,Unverified Rev B
R214,2.67k 1%,SS8:R_0603_1608Metric,1,Unverified Rev B
C219,1nF C0G,SS8:C_0603_1608Metric,1,Unverified Rev B
C222,470uF 35V low ESR,SS8:CP_Radial_D10.0mm_P5.00mm,1,Unverified Rev B
U12,LTC4365ITS8#PBF,SS8:TSOT-23-8,1,Unverified Rev B
Q1,Si9945CDY-T1-GE3,SS8:SOIC-8_3.9x4.9mm_P1.27mm,1,Unverified Rev B
R220,290k 0.1%,SS8:R_0603_1608Metric,1,Unverified Rev B
R221,10k 0.1%,SS8:R_0603_1608Metric,1,Unverified Rev B
R222,340k 0.01%,SS8:R_0603_1608Metric,1,Unverified Rev B
R223,10k 0.01%,SS8:R_0603_1608Metric,1,Unverified Rev B
R224,10k,SS8:R_0603_1608Metric,1,Unverified Rev B
C220,47nF 50V X7R,SS8:C_0603_1608Metric,1,Unverified Rev B
C221,470uF 35V low ESR,SS8:CP_Radial_D10.0mm_P5.00mm,1,Unverified Rev B
F2,0451.750MRL / 750mA 125V,SS8:Fuse_Littelfuse-NANO2-451_453,1,Unverified Rev B
J5,16.8V POWER ARRAY A,SS8:FP_910b6471cdf1,1,Unverified Rev B
F3,0451.750MRL / 750mA 125V,SS8:Fuse_Littelfuse-NANO2-451_453,1,Unverified Rev B
J6,16.8V POWER ARRAY B,SS8:FP_910b6471cdf1,1,Unverified Rev B
R225,10k 0.25W,SS8:R_0805_2012Metric,1,Unverified Rev B
U13,R-78E3.3-0.5,SS8:Converter_DCDC_RECOM_R-78E-0.5_THT,1,Unverified Rev B
C230,10uF 50V X7R,SS8:C_1210_3225Metric,1,Unverified Rev B
C231,10uF 10V X7R,SS8:C_0805_2012Metric,1,Unverified Rev B
C232,100nF 50V X7R,SS8:C_0603_1608Metric,1,Unverified Rev B
R230,330R 0.125W minimum load,SS8:R_0805_2012Metric,1,Unverified Rev B
TP1,GND,SS8:TestPoint_Pad_D1.5mm,1,Unverified Rev B
TP2,+3V3,SS8:TestPoint_Pad_D1.5mm,1,Unverified Rev B
TP3,VIN,SS8:TestPoint_Pad_D1.5mm,1,Unverified Rev B
TP4,VPROT,SS8:TestPoint_Pad_D1.5mm,1,Unverified Rev B
TP5,VREG_16V8,SS8:TestPoint_Pad_D1.5mm,1,Unverified Rev B
TP6,VDRV_SAFE,SS8:TestPoint_Pad_D1.5mm,1,Unverified Rev B
TP7,CORE_OK,SS8:TestPoint_Pad_D1.5mm,1,Unverified Rev B
TP8,A_SCLK,SS8:TestPoint_Pad_D1.5mm,1,Unverified Rev B
TP9,B_SCLK,SS8:TestPoint_Pad_D1.5mm,1,Unverified Rev B
TP10,A_OE_N,SS8:TestPoint_Pad_D1.5mm,1,Unverified Rev B
TP11,B_OE_N,SS8:TestPoint_Pad_D1.5mm,1,Unverified Rev B
